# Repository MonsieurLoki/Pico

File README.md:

# Projet Pico Smart Fan
EPHEC, Technologies de l'Informatique, Electronique 2

Groupe J:
- Gaspard Derruine
- Maxime Malpica
- Hugo Noppe
- Dorian Kwizera

## Table of Contents

- [Introduction](#introduction)
- [Features](#features)
- [GitHub](#GitHub)

## Introduction

This is a group project from Ephec students in TI2, Electronics2

## Features

Project objectives :
- implement several functionalities on a Raspberry Pi Pico W
- monitor a temperature sensor and display it on a 2 digit 7-segment
    - use 2 SN74LS47N to drive the 7-segment digits
- when temperature is above MAX, activate fan until it's down below MAX-1
    - a simple 5v fan (DC motor) is used
    - a relay is used to ensure enough power can be given to the fan
    - (an extra power source is added to the Pico 5V source from the USB cable (or battery))
- a web server on the Pico allows to
    - consult that state of the system (temperature, etc)
    - manually control the fan (ON, OFF)
    - the MAX value can be updated with the web interface
- optional
    - implement an LCD 1602 display to show additional information
    - buzzer when temperature above MAX
    - vary the fan speed depending on the temperature (with PWM)
    - leds to indicate status
    - potentiometer (ADC) to adjust reference temperature
    - etc

## GitHub

https://github.com/MonsieurLoki/Pico

Le repository contient:
- les schémas et circuits du PCB
- le code
- le rapport d'avancement et le rapport final

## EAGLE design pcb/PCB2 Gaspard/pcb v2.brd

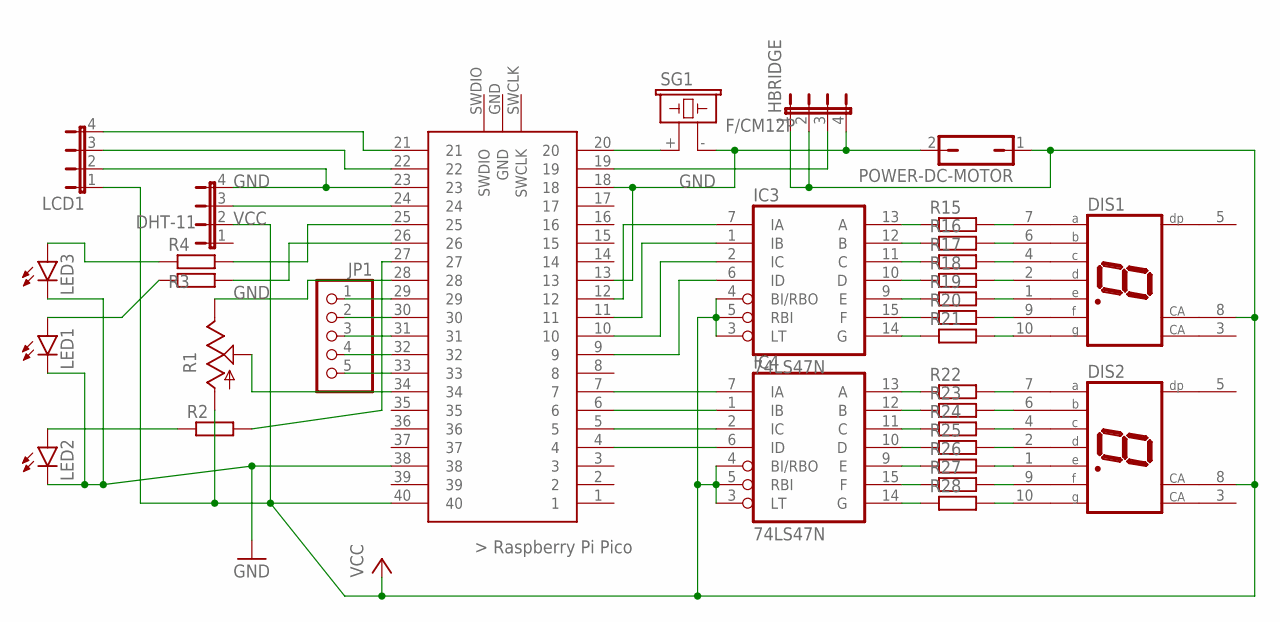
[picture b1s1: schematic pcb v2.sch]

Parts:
DHT-11: JP4E; JP4
DIS1, DIS2: HD-H101; HDSP-M
HBRIDGE: JP4E; JP4
IC3, IC4: 74LS47N; DIL16
JP1: PINHD-1X5; 1X05
LCD1: JP4E; JP4
LED1, LED2, LED3: LED5MM
POWER-DC-MOTOR: JP1Q; JP1
R1: TRIM_US-CA6V; CA6V
R2, R3, R4: R-EU_0207/10; 0207/10
R15, R16, R17, R18, R19, R20, R21, R22, R23, R24, R25, R26, R27, R28: R-EU_0207/12; 0207/12
SG1: F/CM12P
U$1: RASPBERRY-PI-PICO_TH; FT_RASPBERRY-PI-PICO_TH

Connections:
GND: DHT-11.4, HBRIDGE.4, IC3.8 (GND), IC4.8 (GND), LCD1.2, LED1.K (C), LED2.K (C), LED3.K (C), POWER-DC-MOTOR.2, R1.E, SG1.- (2), U$1.13, U$1.18, U$1.23, U$1.28, U$1.38
unnamed: IC4.7 (IA), U$1.7
unnamed: IC4.1 (IB), U$1.6
unnamed: IC4.2 (IC), U$1.5
unnamed: IC4.6 (ID), U$1.4
unnamed: R1.S, U$1.34
unnamed: IC3.14 (G), R21.1
unnamed: DIS2.7 (A), R22.2
unnamed: DIS2.6 (B), R23.2
unnamed: DIS2.4 (C), R24.2
unnamed: DIS2.2 (D), R25.2
unnamed: DIS2.1 (E), R26.2
unnamed: DIS1.10 (G), R21.2
unnamed: IC3.6 (ID), U$1.9
unnamed: IC3.2 (IC), U$1.10
unnamed: IC3.1 (IB), U$1.11
unnamed: IC3.7 (IA), U$1.12
unnamed: DIS2.9 (F), R27.2
unnamed: DIS2.10 (G), R28.2
unnamed: IC4.13 (A), R22.1
unnamed: IC4.12 (B), R23.1
unnamed: IC4.11 (C), R24.1
unnamed: DIS1.7 (A), R15.2
unnamed: DIS1.6 (B), R16.2
unnamed: DIS1.4 (C), R17.2
unnamed: DIS1.2 (D), R18.2
unnamed: DIS1.1 (E), R19.2
unnamed: JP1.1, U$1.29
unnamed: JP1.2, U$1.30
unnamed: IC4.10 (D), R25.1
unnamed: IC4.9 (E), R26.1
unnamed: IC4.15 (F), R27.1
unnamed: IC4.14 (G), R28.1
unnamed: SG1.+ (1), U$1.20
unnamed: JP1.3, U$1.31
unnamed: DIS1.9 (F), R20.2
unnamed: IC3.13 (A), R15.1
unnamed: IC3.12 (B), R16.1
unnamed: IC3.11 (C), R17.1
unnamed: IC3.10 (D), R18.1
unnamed: IC3.9 (E), R19.1
unnamed: IC3.15 (F), R20.1
unnamed: HBRIDGE.3, U$1.19
unnamed: JP1.4, U$1.32
unnamed: DHT-11.3, U$1.24
unnamed: LCD1.4, U$1.21
unnamed: LCD1.3, U$1.22
unnamed: JP1.5, U$1.33
unnamed: R2.2, U$1.27
unnamed: R4.2, U$1.25
unnamed: R3.2, U$1.26
unnamed: LED2.A, R2.1
unnamed: LED1.A, R3.1
unnamed: LED3.A, R4.1
VCC: DHT-11.2, DIS1.8 (CA), DIS2.8 (CA), HBRIDGE.1, HBRIDGE.2, IC3.3 (LT), IC3.4 (BI/RBO), IC3.5 (RBI), IC3.16 (VCC), IC4.3 (LT), IC4.4 (BI/RBO), IC4.5 (RBI), IC4.16 (VCC), LCD1.1, POWER-DC-MOTOR.1, R1.A, U$1.40

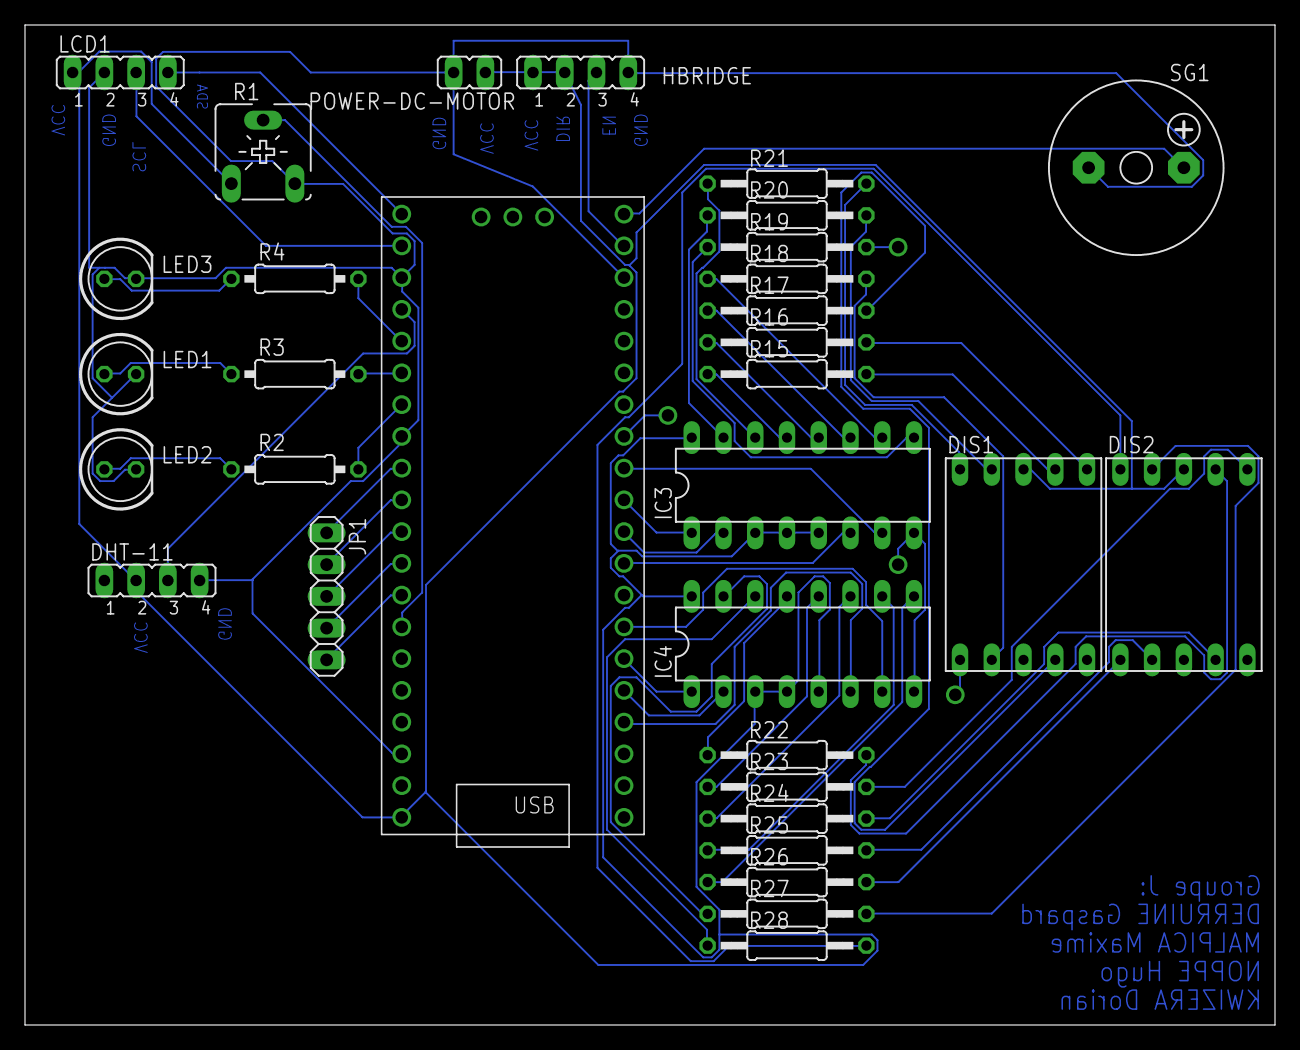
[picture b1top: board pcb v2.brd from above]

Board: 2 copper layers, 100.0 x 80.0 mm, 32 parts (0 on the bottom side), 55 nets.

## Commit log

2024-03-16 Create shémas
2024-03-16 Create code-test-composants
2024-03-16 Create final-code
2024-03-16 ajout shéma
2024-03-16 suppression du fichier test.txt
2024-03-16 improved readme
2024-03-17 update schémas
2024-03-17 suppression fichier temp
2024-03-17 finetuning
2024-03-18 update after check drc erc
2024-03-19 update isolate width
2024-03-19 ajout de tout les fichiers dans archives et la version finale dans pcb2 gaspard
